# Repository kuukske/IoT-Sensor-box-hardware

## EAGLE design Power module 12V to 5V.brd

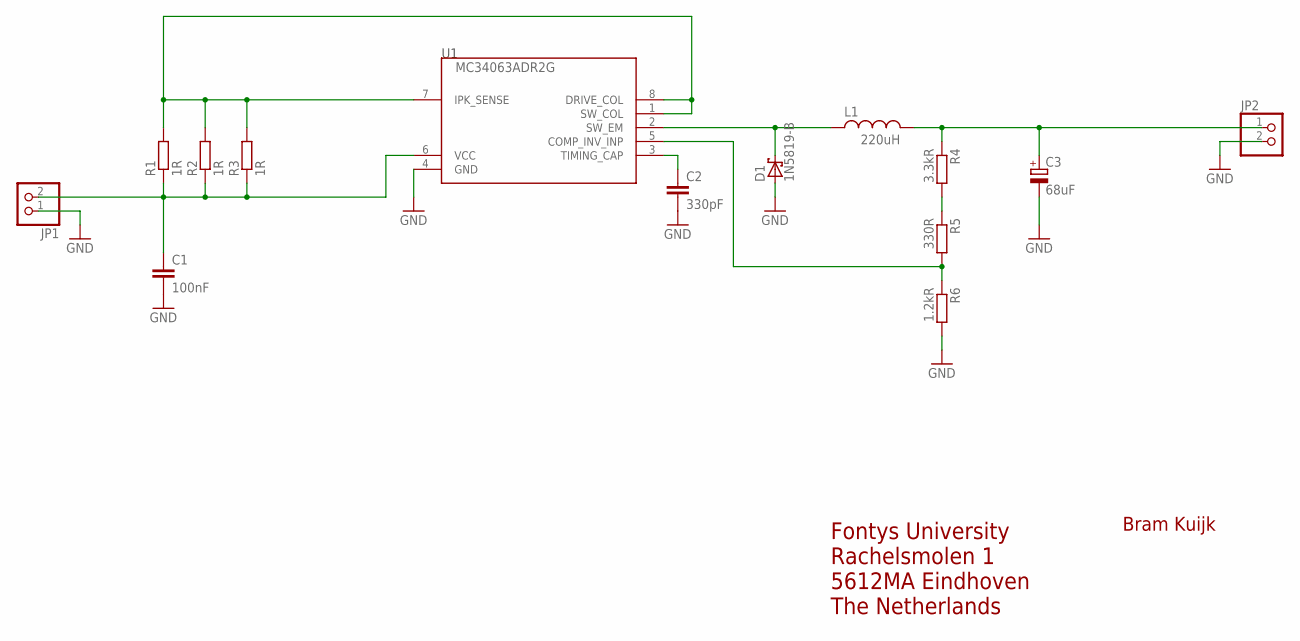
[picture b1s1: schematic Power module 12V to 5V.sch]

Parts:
C1: 100nF; C050-045X075
C2: 330pF; C050-045X075
C3: 68uF; E2,5-7
D1: 1N5819-B; DO41-7.6
JP1, JP2: PINHD-1X2; 1X02
L1: 220uH; SRR1208_L
R1, R2, R3: 1R; 0207/10
R4: 3.3kR; 0207/10
R5: 330R; 0207/10
R6: 1.2kR; 0207/10
U1: MC34063ADR2G; SOIC8

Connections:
GND: C1.2, C2.2, C3.-, D1.A, JP1.1, JP2.2, R6.2, U1.4 (GND)
unnamed: C1.1, JP1.2, R1.1, R2.1, R3.1, U1.6 (VCC)
unnamed: R1.2, R2.2, R3.2, U1.1 (SW_COL), U1.7 (IPK_SENSE), U1.8 (DRIVE_COL)
unnamed: D1.C, L1.P$1 (1), U1.2 (SW_EM)
unnamed: C3.+, JP2.1, L1.P$2 (2), R4.1
unnamed: C2.1, U1.3 (TIMING_CAP)
unnamed: R5.2, R6.1, U1.5 (COMP_INV_INP)
unnamed: R4.2, R5.1

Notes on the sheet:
Bram Kuijk
Fontys University Rachelsmolen 1 5612MA Eindhoven The Netherlands

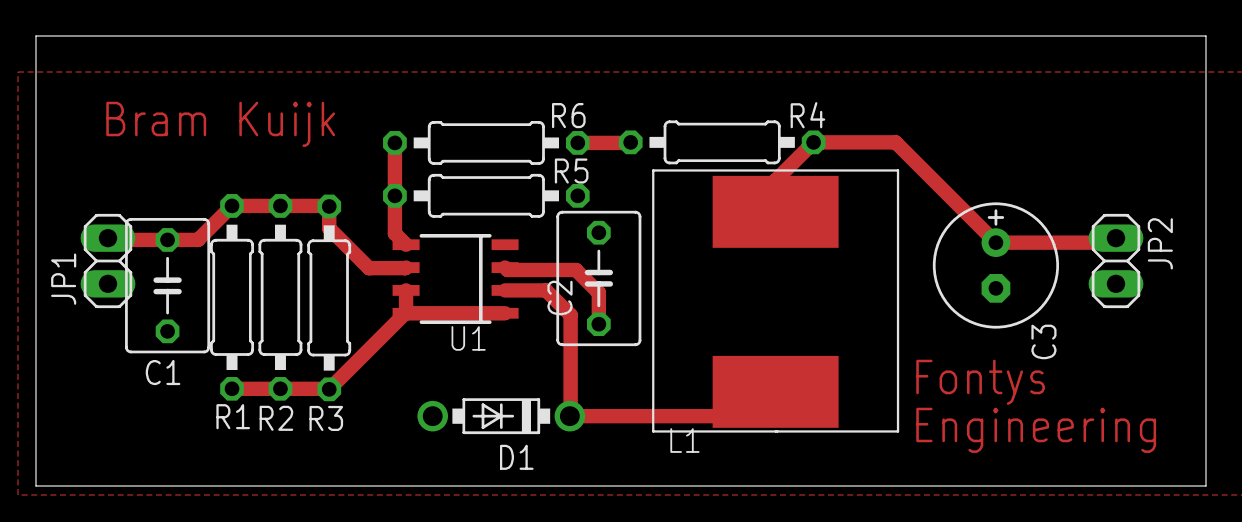
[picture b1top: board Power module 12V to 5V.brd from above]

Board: 2 copper layers, 65.0 x 25.0 mm, 14 parts (0 on the bottom side), 8 nets.

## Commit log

2018-06-12 Added BeCreative EAGLE library for tutorial
